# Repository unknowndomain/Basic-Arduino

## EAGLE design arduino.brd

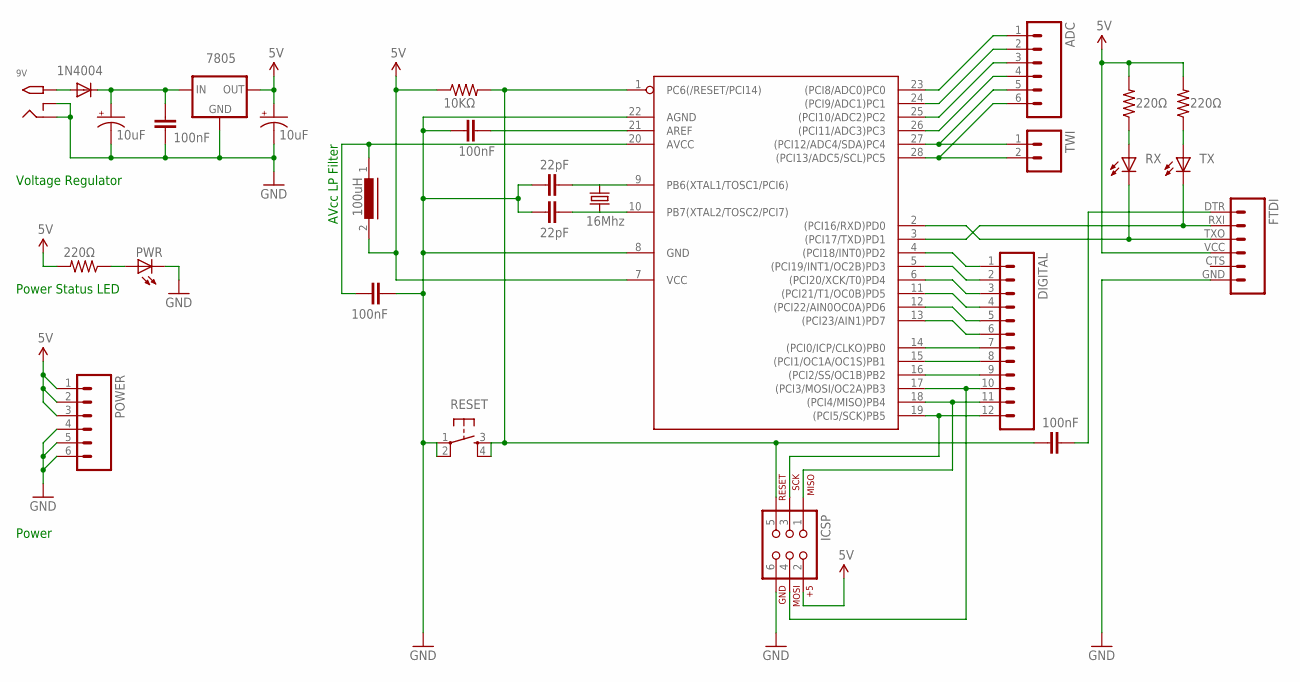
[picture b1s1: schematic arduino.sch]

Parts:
9V: 2.1MMJACKTHM; PJ-102A
ADC: M06LOCK; 1X06_LOCK
AVR_C1, AVR_C4, AVR_C5: 100nF; CAP-PTH-5MM
AVR_C2, AVR_C3: 22pF; CAP-PTH-5MM
AVR_R1: 10KΩ; AXIAL-0.4
AVR_R2, AVR_R3: 220Ω; AXIAL-0.4
D1: 1N4004; DO41-10
DIGITAL: M12LOCK; 1X12_LOCK
FTDI: FTDI_BASICPTH; FTDI_BASIC
IC1: ATMEGA168-20P; DIL28-3
IC2: 7805; 78XXL
ICSP: AVR_SPI_PRG_62X3_LOCK; 2X3_LOCK
L1: 100uH; MCC10
POWER: M06LOCK; 1X06_LOCK
PWR: LED5MM
PWR_C1, PWR_C3: 10uF; CPOL-RADIAL-10UF-25V
PWR_C2: 100nF; CAP-PTH-5MM
PWR_R1: 220Ω; AXIAL-0.4
Q1: 16Mhz; HC49/S
RESET: TAC_SWITCHPTH; TACTILE-PTH
RX: LED5MM
TWI: M02LOCK; 1X02_LOCK
TX: LED5MM

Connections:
5V: AVR_R1.P$1 (1), AVR_R2.P$2 (2), AVR_R3.P$2 (2), FTDI.VCC (4), IC1.7 (VCC), IC2.OUT, ICSP.2, L1.2, POWER.1, POWER.2, POWER.3, PWR_C3.1 (+), PWR_R1.P$2 (2)
ADC0: ADC.1, IC1.23 ((PCI8/ADC0)PC0)
ADC1: ADC.2, IC1.24 ((PCI9/ADC1)PC1)
ADC2: ADC.3, IC1.25 ((PCI10/ADC2)PC2)
ADC3: ADC.4, IC1.26 ((PCI11/ADC3)PC3)
AREF: AVR_C1.2, IC1.21 (AREF)
AVCC: AVR_C4.2, IC1.20 (AVCC), L1.1
GND: 9V.RING, 9V.RING_SW, AVR_C1.1, AVR_C2.1, AVR_C3.1, AVR_C4.1, FTDI.GND (6), IC1.8 (GND), IC1.22 (AGND), IC2.GND, ICSP.6, POWER.4, POWER.5, POWER.6, PWR.K (C), PWR_C1.2 (-), PWR_C2.1, PWR_C3.2 (-), RESET.1, RESET.2
MISO: DIGITAL.11, IC1.18 ((PCI4/MISO)PB4), ICSP.1
MOSI: DIGITAL.10, IC1.17 ((PCI3/MOSI/OC2A)PB3), ICSP.4
unnamed: AVR_R2.P$1 (1), RX.A
unnamed: AVR_R3.P$1 (1), TX.A
unnamed: PWR.A, PWR_R1.P$1 (1)
unnamed: AVR_C5.2, FTDI.DTR (1)
unnamed: 9V.TIP, D1.A
unnamed: DIGITAL.1, IC1.4 ((PCI18/INT0)PD2)
unnamed: DIGITAL.2, IC1.5 ((PCI19/INT1/OC2B)PD3)
unnamed: DIGITAL.3, IC1.6 ((PCI20/XCK/T0)PD4)
unnamed: DIGITAL.4, IC1.11 ((PCI21/T1/OC0B)PD5)
unnamed: DIGITAL.5, IC1.12 ((PCI22/AIN0OC0A)PD6)
unnamed: DIGITAL.6, IC1.13 ((PCI23/AIN1)PD7)
unnamed: DIGITAL.7, IC1.14 ((PCI0/ICP/CLKO)PB0)
unnamed: DIGITAL.8, IC1.15 ((PCI1/OC1A/OC1S)PB1)
unnamed: DIGITAL.9, IC1.16 ((PCI2/SS/OC1B)PB2)
RESET: AVR_C5.1, AVR_R1.P$2 (2), IC1.1 (PC6(/RESET/PCI14)), ICSP.5, RESET.3, RESET.4
RX: FTDI.TXO (3), IC1.2 ((PCI16/RXD)PD0), RX.K (C)
SCK: DIGITAL.12, IC1.19 ((PCI5/SCK)PB5), ICSP.3
SCL: ADC.6, IC1.28 ((PCI13/ADC5/SCL)PC5), TWI.2
SDA: ADC.5, IC1.27 ((PCI12/ADC4/SDA)PC4), TWI.1
TX: FTDI.RXI (2), IC1.3 ((PCI17/TXD)PD1), TX.K (C)
VCC: D1.C, IC2.IN, PWR_C1.1 (+), PWR_C2.2
XTAL1: AVR_C2.2, IC1.9 (PB6(XTAL1/TOSC1/PCI6)), Q1.2
XTAL2: AVR_C3.2, IC1.10 (PB7(XTAL2/TOSC2/PCI7)), Q1.1

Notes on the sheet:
Voltage Regulator
Power Status LED
AVcc LP Filter
Power

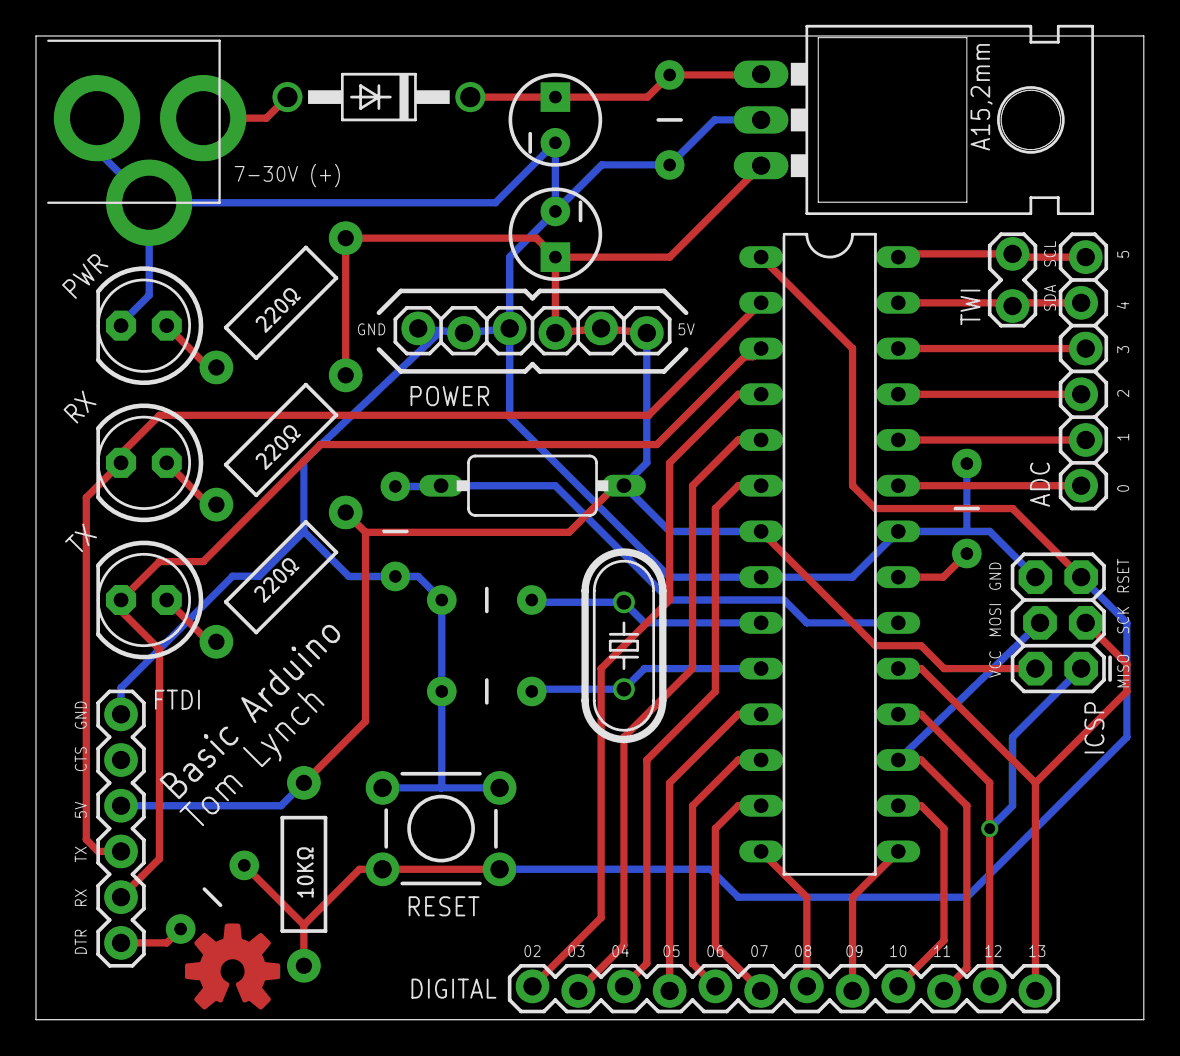
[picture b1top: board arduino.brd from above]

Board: 2 copper layers, 61.5 x 54.7 mm, 29 parts (0 on the bottom side), 33 nets.

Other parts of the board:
U$7: OSHWLOGO_TOP_0.2

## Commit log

2012-12-04 First commit.
2012-12-05 Added simple readme.txt

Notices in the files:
parts and their libraries:
SparkFun: Licensing: CC v3.0 Share-Alike You are welcome to use this library for commercial purposes.
